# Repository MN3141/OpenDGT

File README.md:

# OpenDGT
Repository for implementing communication between DGT 3000 Chess Clock and PC.

## Depencies
### Main documentation
In order to be able to compile the bachelor thesis files (which shall serve as the main documentation) you would need a LaTeX compiler. The development of this project has been done using `TeXLive` package.

### UML diagrams
In order to compile the UML files written in PlantUML you would need the following tools:
- Java Runtime Environment
- [PlantUML JAR file](https://plantuml.com/download)

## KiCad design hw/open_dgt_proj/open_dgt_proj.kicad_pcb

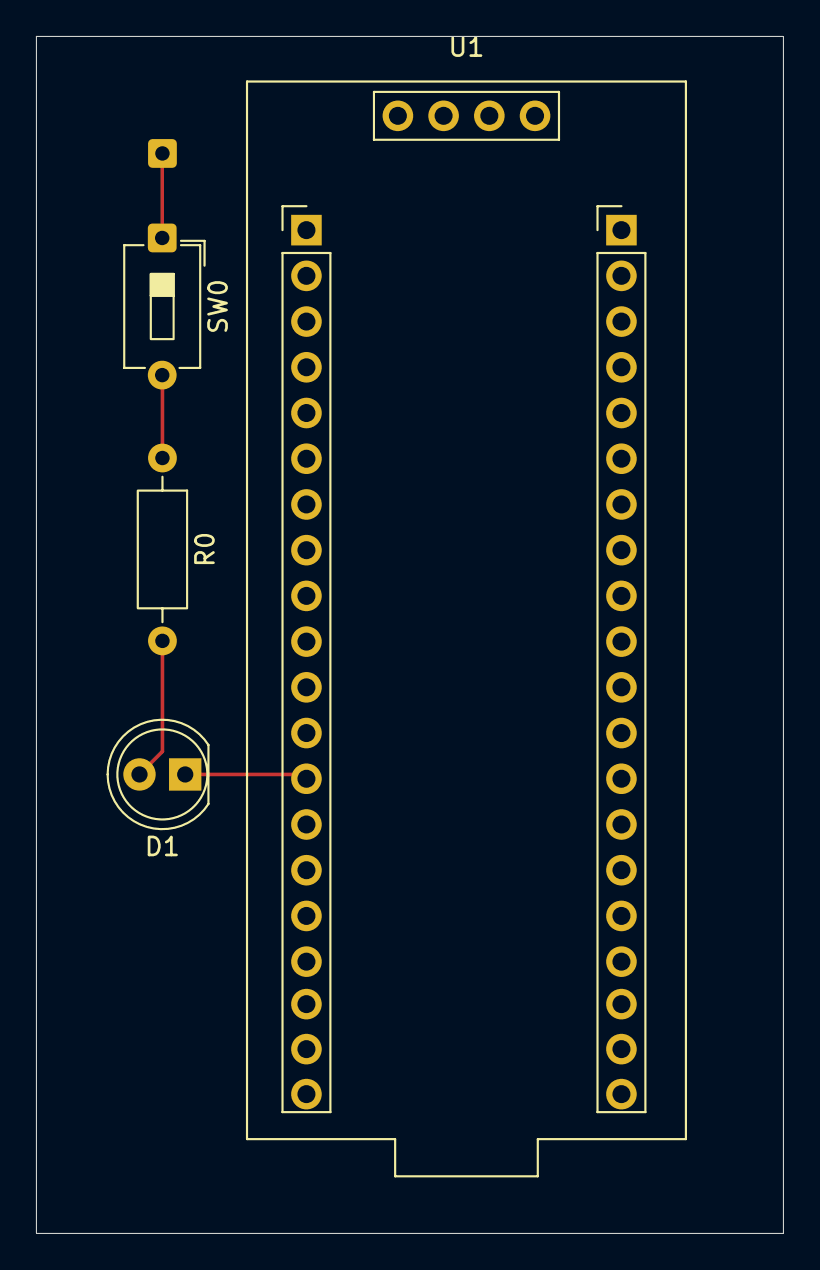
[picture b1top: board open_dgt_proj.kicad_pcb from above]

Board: 2 copper layers, 41.5 x 66.5 mm, 4 parts (0 on the bottom side), 4 nets.

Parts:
D1: LED; LED_D5.0mm_FlatTop
R0: 220; R_Axial_DIN0207_L6.3mm_D2.5mm_P10.16mm_Horizontal
SW0: SW_DIP_x01; SW_DIP_SPSTx01_Slide_6.7x4.1mm_W7.62mm_P2.54mm_LowProfile
U1: MiniF4-STM32F401CEU6; YAAJ_BlackPill_SWD_2

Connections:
/DGT0_SDA: U1.12 (PB4), U1.15 (PB7)
unnamed: D1.2 (A), R0.2
unnamed: D1.1 (K), U1.13 (PB5), U1.14 (PB6)
unnamed: R0.1, SW0.2

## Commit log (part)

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2025-11-24 Update README to include image and remove text
    Removed project title and description, added image.
2026-02-18 Added basic files for project schematic
2026-02-21 Updated project schematic, PCB and 3D model
2026-02-21 Added MIT License to the project
2026-04-10 Added basic project structure and requirements
2026-04-10 Listed LaTeX compiler dependency
2026-04-10 Added basic UML diagrams
2026-04-10 Added STM32F411CEU6 files for HAL and USB
2026-04-10 Added stub for HAL and OpenDGTLib
2026-04-10 Fixed build errors for missing file
2026-04-12 Added basic HAL for STM32F411
2026-04-12 Added basic USB TX
2026-04-12 Solved GPIO_Init bug
2026-04-13 Added basic USB RX logic
2026-04-13 Removed unnecessary STM32 chips and IAR compiler specific files
2026-04-13 Removed unnecessary startup files
2026-04-13 Added USB sample application for STM32F411 (#27)
    * Added STM32F411CEU6 files for HAL and USB
    * Added stub for HAL and OpenDGTLib
    * Fixed build errors for missing file
    * Added basic HAL for STM32F411
    * Added basic USB TX
    * Solved GPIO_Init bug
2026-04-13 Added basic structure for thesis paper
2026-04-13 Added introduction section
2026-04-14 Microcontroller page
2026-04-14 Info regarding selected microcontroller
2026-04-14 Ecosystem section update
2026-04-17 Updated schematic for DGT3000 jack connection
2026-04-17 Added info regarding dgt3000 hw
2026-04-17 Corrected minor mistake
2026-04-18 Added symbol for STM8L152M8 used in DGT clock
2026-04-18 Updated schematic for DGT3000 clock
2026-04-18 Document DGT3000 clock HW (#28)
    * Updated schematic for DGT3000 jack connection
    * Added info regarding dgt3000 hw
    * Corrected minor mistake
    * Added symbol for STM8L152M8 used in DGT clock
    * Updated schematic for DGT3000 clock
    ---------
2026-06-05 Updated references section
2026-06-06 Added section about chess clocks
2026-06-07 Info about Pichochess
2026-06-07 Draft for setup section
2026-06-08 Added draft for system vision
2026-06-08 Added system schematic + KiCAD version update
2026-06-18 Added the rest of Jack connections
2026-06-22 Added the rest of Jack connections (#30)
2026-06-22 Added demo for I2C1 peripheral
2026-06-22 DGT wake func
2026-06-22 Revised Current Solutions chapter
